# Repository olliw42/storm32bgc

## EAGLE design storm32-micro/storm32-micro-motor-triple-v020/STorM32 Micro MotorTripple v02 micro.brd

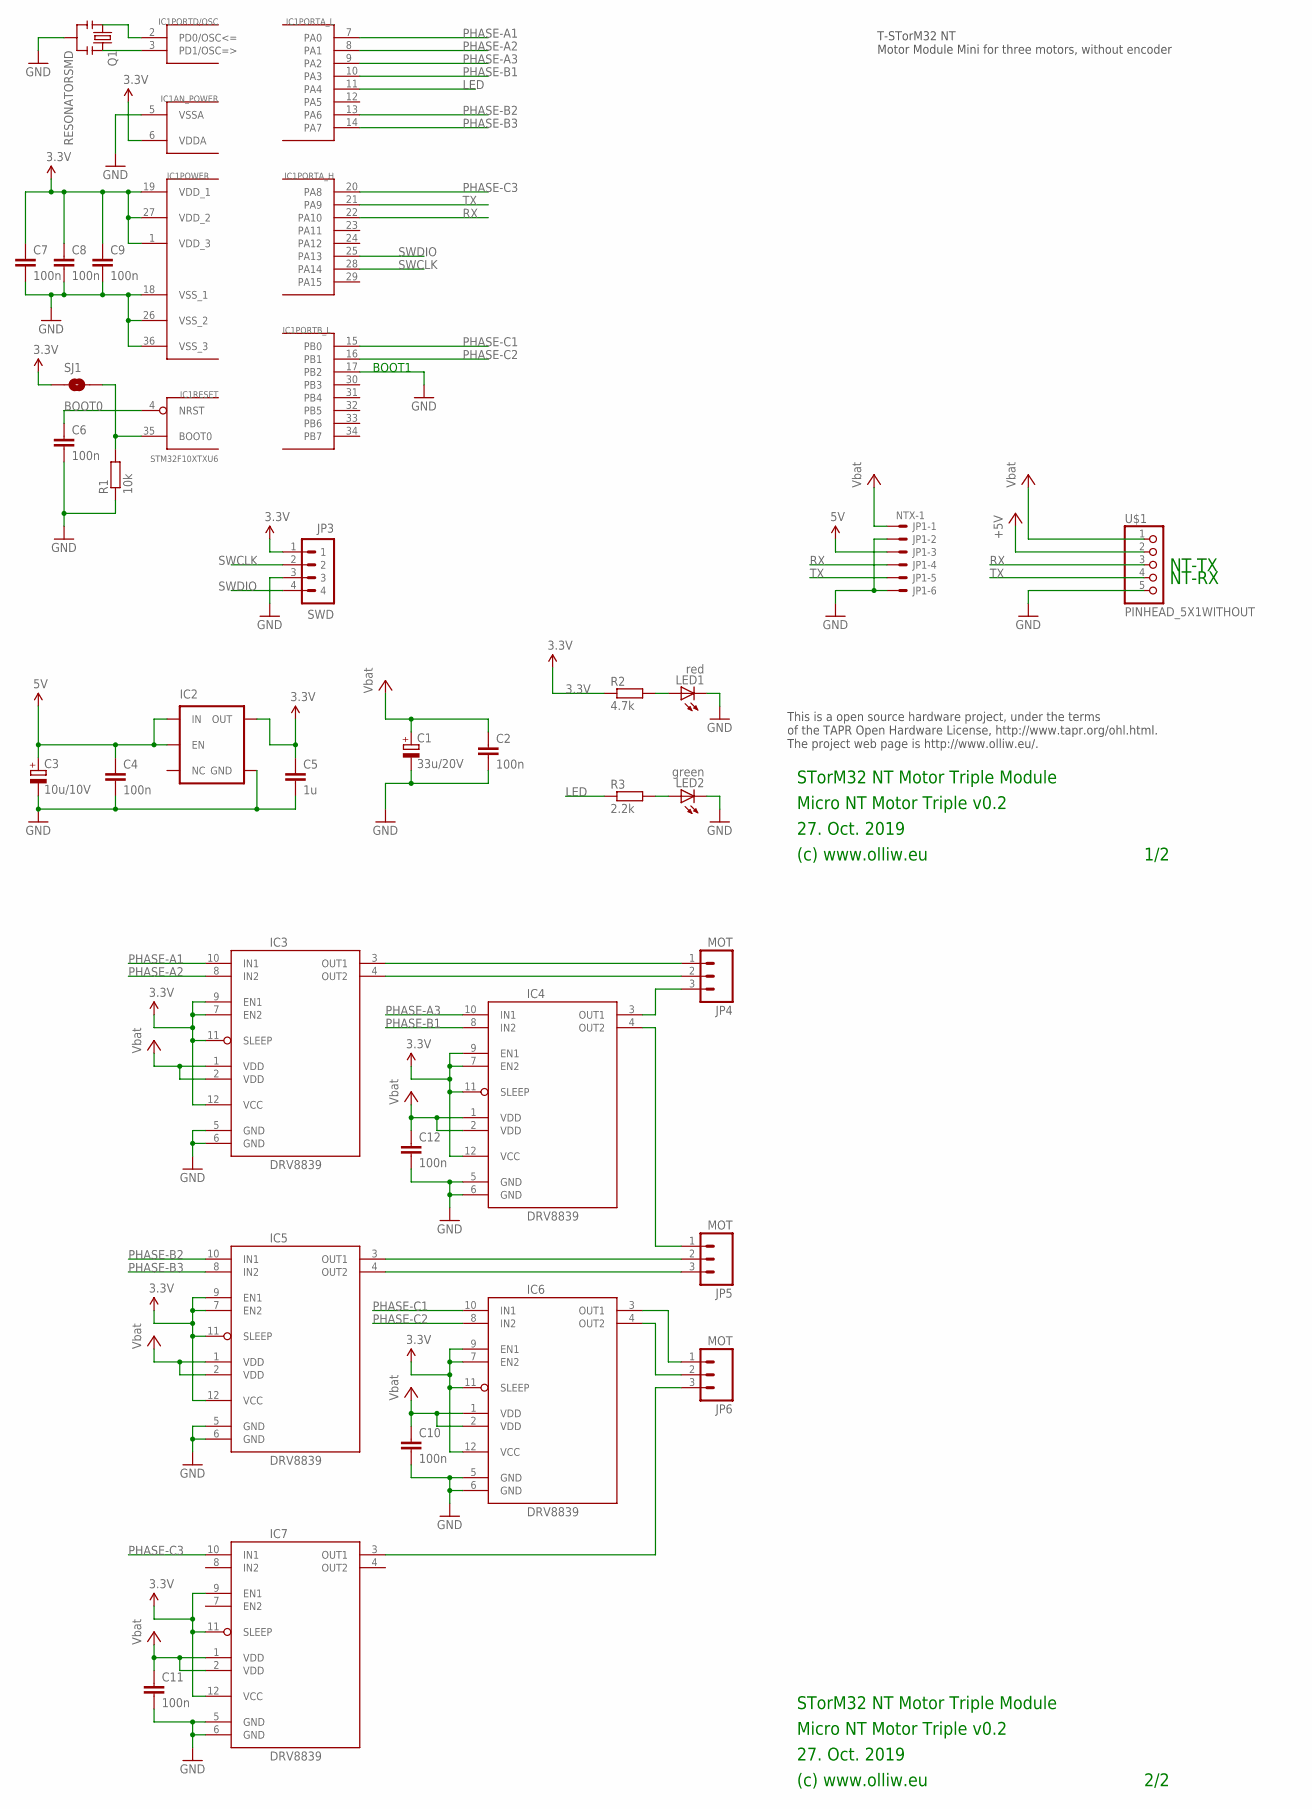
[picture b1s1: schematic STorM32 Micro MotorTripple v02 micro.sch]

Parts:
C1: 33u/20V; SMC_B
C2, C10, C11, C12: 100n; C0603
C3: 10u/10V; SMC_A
C4, C6, C7, C8, C9: 100n; C0402
C5: 1u; C0603
IC1: STM32F10XTXU6; VFQFPN36
IC2: V_REG_TPS76433SOT23-5; SOT23-5
IC3, IC4, IC5, IC6, IC7: DRV8839; WSON-12-2X3MM
JP1: NTX-1; SM06B-SRSS-TB
JP3: SWD; 4X1_1P27_OCT_BILEX
JP4, JP5, JP6: MOT; 1X03
LED1: red; CHIPLED_0603
LED2: green; CHIPLED_0603
Q1: RESONATORSMD; RESONATOR-SMD
R1: 10k; R0402
R2: 4.7k; R0402
R3: 2.2k; R0402
SJ1: BOOT0; SJ_2S-NO
U$1: PINHEAD_5X1WITHOUT; PINHEAD_5X1_WO

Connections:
3.3V: C5.1, C7.1, C8.1, C9.1, IC1.1 (VDD_3), IC1.6 (VDDA), IC1.19 (VDD_1), IC1.27 (VDD_2), IC2.5 (OUT), IC3.7 (EN2), IC3.9 (EN1), IC3.11 (SLEEP), IC3.12 (VCC), IC4.7 (EN2), IC4.9 (EN1), IC4.11 (SLEEP), IC4.12 (VCC), IC5.7 (EN2), IC5.9 (EN1), IC5.11 (SLEEP), IC5.12 (VCC), IC6.7 (EN2), IC6.9 (EN1), IC6.11 (SLEEP), IC6.12 (VCC), IC7.9 (EN1), IC7.11 (SLEEP), IC7.12 (VCC), JP3.1, R2.1, SJ1.1
5V: C3.+, C4.1, IC2.1 (IN), IC2.3 (EN), JP1.3, U$1.2
GND: C1.-, C2.2, C3.-, C4.2, C5.2, C6.2, C7.2, C8.2, C9.2, C10.2, C11.2, C12.2, IC1.5 (VSSA), IC1.17 (PB2), IC1.18 (VSS_1), IC1.26 (VSS_2), IC1.36 (VSS_3), IC2.2 (GND), IC3.5 (GND), IC3.6 (GND), IC4.5 (GND), IC4.6 (GND), IC5.5 (GND), IC5.6 (GND), IC6.5 (GND), IC6.6 (GND), IC7.5 (GND), IC7.6 (GND), JP1.2, JP1.6, JP3.3, LED1.C, LED2.C, Q1.2, R1.1, U$1.5
LED: IC1.11 (PA4), R3.1
unnamed: IC4.3 (OUT1), JP4.3
unnamed: C6.1, IC1.4 (NRST)
unnamed: IC1.35 (BOOT0), R1.2, SJ1.2
unnamed: IC1.2 (PD0/OSC<=), Q1.1
unnamed: IC1.3 (PD1/OSC=>), Q1.3
unnamed: LED1.A, R2.2
unnamed: LED2.A, R3.2
unnamed: IC6.3 (OUT1), JP6.1
unnamed: IC3.4 (OUT2), JP4.2
unnamed: IC3.3 (OUT1), JP4.1
unnamed: IC5.3 (OUT1), JP5.2
unnamed: IC4.4 (OUT2), JP5.1
unnamed: IC5.4 (OUT2), JP5.3
unnamed: IC6.4 (OUT2), JP6.2
unnamed: IC7.3 (OUT1), JP6.3
PHASE-A1: IC1.7 (PA0), IC3.10 (IN1)
PHASE-A2: IC1.8 (PA1), IC3.8 (IN2)
PHASE-A3: IC1.9 (PA2), IC4.10 (IN1)
PHASE-B1: IC1.10 (PA3), IC4.8 (IN2)
PHASE-B2: IC1.13 (PA6), IC5.10 (IN1)
PHASE-B3: IC1.14 (PA7), IC5.8 (IN2)
PHASE-C1: IC1.15 (PB0), IC6.10 (IN1)
PHASE-C2: IC1.16 (PB1), IC6.8 (IN2)
PHASE-C3: IC1.20 (PA8), IC7.10 (IN1)
RX: IC1.22 (PA10), JP1.4, U$1.3
SWCLK: IC1.28 (PA14), JP3.2
SWDIO: IC1.25 (PA13), JP3.4
TX: IC1.21 (PA9), JP1.5, U$1.4
VCCG: C1.+, C2.1, C10.1, C11.1, C12.1, IC3.1 (VDD), IC3.2 (VDD), IC4.1 (VDD), IC4.2 (VDD), IC5.1 (VDD), IC5.2 (VDD), IC6.1 (VDD), IC6.2 (VDD), IC7.1 (VDD), IC7.2 (VDD), JP1.1, U$1.1

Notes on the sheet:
27. Oct. 2019
(c) www.olliw.eu
STorM32 NT Motor Triple Module
Micro NT Motor Triple v0.2
T-STorM32 NT Motor Module Mini for three motors, without encoder
BOOT1
NT-TX
NT-RX
This is a open source hardware project, under the terms of the TAPR Open Hardware License, http://www.tapr.org/ohl.html. The project web page is http://www.olliw.eu/.
1/2
2/2

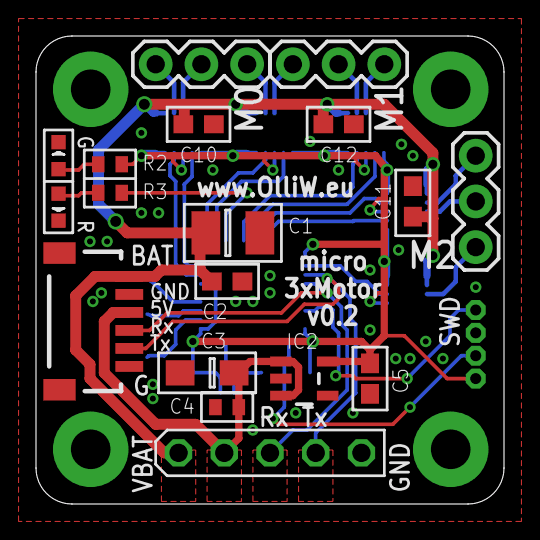
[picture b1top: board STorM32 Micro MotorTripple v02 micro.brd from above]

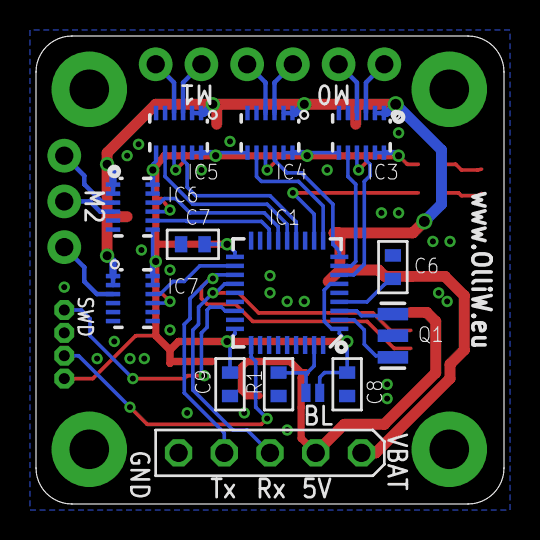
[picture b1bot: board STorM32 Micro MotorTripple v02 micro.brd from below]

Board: 2 copper layers, 26.0 x 26.0 mm, 32 parts (14 on the bottom side), 33 nets.

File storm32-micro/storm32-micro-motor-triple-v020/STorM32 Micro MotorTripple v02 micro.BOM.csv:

"Part";"Value";"Device";"Package";"Description";"";
"C1";"33u/20V";"CPOL-EUSMCB";"SMC_B";"POLARIZED CAPACITOR, European symbol";"";
"C2";"100n";"C-EUC0603";"C0603";"CAPACITOR, European symbol";"";
"C3";"10u/10V";"CPOL-EUSMCA";"SMC_A";"POLARIZED CAPACITOR, European symbol";"";
"C4";"100n";"C-EUC0402";"C0402";"CAPACITOR, European symbol";"";
"C5";"1u";"C-EUC0603";"C0603";"CAPACITOR, European symbol";"";
"C6";"100n";"C-EUC0402";"C0402";"CAPACITOR, European symbol";"";
"C7";"100n";"C-EUC0402";"C0402";"CAPACITOR, European symbol";"";
"C8";"100n";"C-EUC0402";"C0402";"CAPACITOR, European symbol";"";
"C9";"100n";"C-EUC0402";"C0402";"CAPACITOR, European symbol";"";
"C10";"100n";"C-EUC0603";"C0603";"CAPACITOR, European symbol";"";
"C11";"100n";"C-EUC0603";"C0603";"CAPACITOR, European symbol";"";
"C12";"100n";"C-EUC0603";"C0603";"CAPACITOR, European symbol";"";
"IC1";"STM32F10XTXU6";"STM32F10XTXU6";"VFQFPN36";"STM32F101/103 36pad VFQPFN36";"";
"IC2";"";"V_REG_TPS76433SOT23-5";"SOT23-5";"Voltage Regulator";"";
"IC3";"DRV8839";"DRV8839";"WSON-12-2X3MM";"";"";
"IC4";"DRV8839";"DRV8839";"WSON-12-2X3MM";"";"";
"IC5";"DRV8839";"DRV8839";"WSON-12-2X3MM";"";"";
"IC6";"DRV8839";"DRV8839";"WSON-12-2X3MM";"";"";
"IC7";"DRV8839";"DRV8839";"WSON-12-2X3MM";"";"";
"JP1";"NTX-1";"SM06B-SRSS-TB";"SM06B-SRSS-TB";"Disconnectable Crimp style connector, 1.0mm pitch6 contacts";"";
"JP3";"SWD";"P4X1_1P27-OCT_BILEX";"4X1_1P27_OCT_BILEX";"";"";
"JP4";"MOT";"M03PTH";"1X03";"Header 3";"";
"JP5";"MOT";"M03PTH";"1X03";"Header 3";"";
"JP6";"MOT";"M03PTH";"1X03";"Header 3";"";
"LED1";"red";"LEDCHIPLED_0603";"CHIPLED_0603";"LED";"";
"LED2";"green";"LEDCHIPLED_0603";"CHIPLED_0603";"LED";"";
"Q1";"RESONATORSMD";"RESONATORSMD";"RESONATOR-SMD";"Resonator";"";
"R1";"10k";"R-EU_R0402";"R0402";"RESISTOR, European symbol";"";
"R2";"4.7k";"R-EU_R0402";"R0402";"RESISTOR, European symbol";"";
"R3";"2.2k";"R-EU_R0402";"R0402";"RESISTOR, European symbol";"";
"SJ1";"BOOT0";"SOLDERJUMPERNO";"SJ_2S-NO";"Solder Jumper";"";
"U$1";"PINHEAD_5X1WITHOUT";"PINHEAD_5X1WITHOUT";"PINHEAD_5X1_WO";"";"";

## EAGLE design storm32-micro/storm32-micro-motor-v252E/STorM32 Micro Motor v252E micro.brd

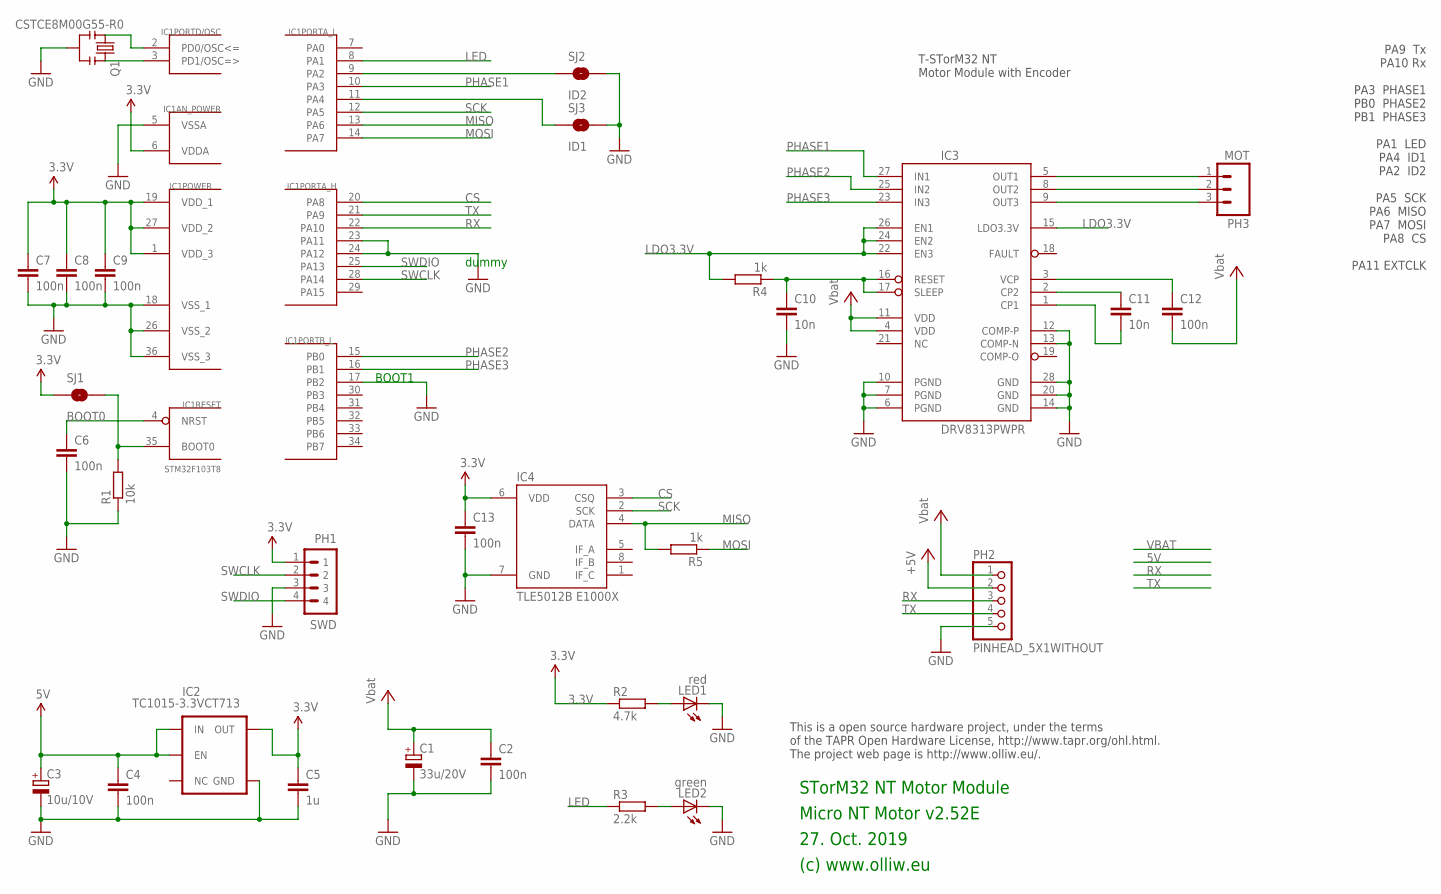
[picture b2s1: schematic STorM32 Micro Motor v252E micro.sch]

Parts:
C1: 33u/20V; SMC_C
C2, C4, C12: 100n; C0603
C3: 10u/10V; SMC_B
C5: 1u; C0603
C6, C7, C8, C9, C13: 100n; C0402
C10: 10n; C0402
C11: 10n; C0603
IC1: STM32F103T8; VFQFPN36
IC2: TC1015-3.3VCT713; SOT23-5
IC3: DRV8313PWPR; HTSSOP28
IC4: TLE5012B E1000X; SO08
LED1: red; CHIPLED_0603
LED2: green; CHIPLED_0603
PH1: SWD; 4X1_1P27_OCT_BILEX
PH2: PINHEAD_5X1WITHOUT; PINHEAD_5X1_WO
PH3: MOT; 1X03_NO_SILK
Q1: CSTCE8M00G55-R0; RESONATOR-SMD
R1: 10k; R0402
R2: 4.7k; R0402
R3: 2.2k; R0402
R4, R5: 1k; R0402
SJ1: BOOT0; SJ_2S-NO
SJ2: ID2; SJ_2S-NO
SJ3: ID1; SJ_2S-NO

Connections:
3.3V: C5.1, C7.1, C8.1, C9.1, C13.1, IC1.1 (VDD_3), IC1.6 (VDDA), IC1.19 (VDD_1), IC1.27 (VDD_2), IC2.5 (OUT), IC4.6 (VDD), PH1.1, R2.1, SJ1.1
5V: C3.+, C4.1, IC2.1 (IN), IC2.3 (EN), PH2.2
CS: IC1.20 (PA8), IC4.3 (CSQ)
GND: C1.-, C2.2, C3.-, C4.2, C5.2, C6.2, C7.2, C8.2, C9.2, C10.2, C13.2, IC1.5 (VSSA), IC1.17 (PB2), IC1.18 (VSS_1), IC1.23 (PA11), IC1.24 (PA12), IC1.26 (VSS_2), IC1.36 (VSS_3), IC2.2 (GND), IC3.6 (PGND), IC3.7 (PGND), IC3.10 (PGND), IC3.12 (COMP-P), IC3.13 (COMP-N), IC3.14 (GND), IC3.20 (GND), IC3.28 (GND), IC4.7 (GND), LED1.C, LED2.C, PH1.3, PH2.5, Q1.2, R1.1, SJ2.2, SJ3.2
LDO3.3V: IC3.15 (LDO3.3V), IC3.22 (EN3), IC3.24 (EN2), IC3.26 (EN1), R4.2
LED: IC1.8 (PA1), R3.1
M1: IC3.5 (OUT1), PH3.1
M2: IC3.8 (OUT2), PH3.2
M3: IC3.9 (OUT3), PH3.3
MISO: IC1.13 (PA6), IC4.4 (DATA), R5.2
MOSI: IC1.14 (PA7), R5.1
unnamed: IC1.9 (PA2), SJ2.1
unnamed: IC1.11 (PA4), SJ3.1
unnamed: C6.1, IC1.4 (NRST)
unnamed: IC1.35 (BOOT0), R1.2, SJ1.2
unnamed: IC1.2 (PD0/OSC<=), Q1.1
unnamed: IC1.3 (PD1/OSC=>), Q1.3
unnamed: LED1.A, R2.2
unnamed: LED2.A, R3.2
unnamed: C11.1, IC3.2 (CP2)
unnamed: C11.2, IC3.1 (CP1)
unnamed: C10.1, IC3.16 (RESET), IC3.17 (SLEEP), R4.1
unnamed: C12.1, IC3.3 (VCP)
PHASE1: IC1.10 (PA3), IC3.27 (IN1)
PHASE2: IC1.15 (PB0), IC3.25 (IN2)
PHASE3: IC1.16 (PB1), IC3.23 (IN3)
RX: IC1.22 (PA10), PH2.3
SCK: IC1.12 (PA5), IC4.2 (SCK)
SWCLK: IC1.28 (PA14), PH1.2
SWDIO: IC1.25 (PA13), PH1.4
TX: IC1.21 (PA9), PH2.4
VBAT: C1.+, C2.1, C12.2, IC3.4 (VDD), IC3.11 (VDD), PH2.1

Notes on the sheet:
27. Oct. 2019
(c) www.olliw.eu
STorM32 NT Motor Module
Micro NT Motor v2.52E
This is a open source hardware project, under the terms of the TAPR Open Hardware License, http://www.tapr.org/ohl.html. The project web page is http://www.olliw.eu/.
T-STorM32 NT Motor Module with Encoder
BOOT1
PA9 Tx PA10 Rx PA3 PHASE1 PB0 PHASE2 PB1 PHASE3 PA1 LED PA4 ID1 PA2 ID2 PA5 SCK PA6 MISO PA7 MOSI PA8 CS PA11 EXTCLK
dummy

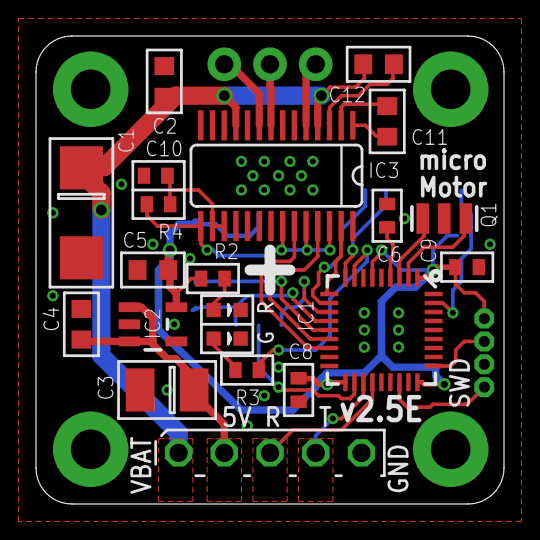
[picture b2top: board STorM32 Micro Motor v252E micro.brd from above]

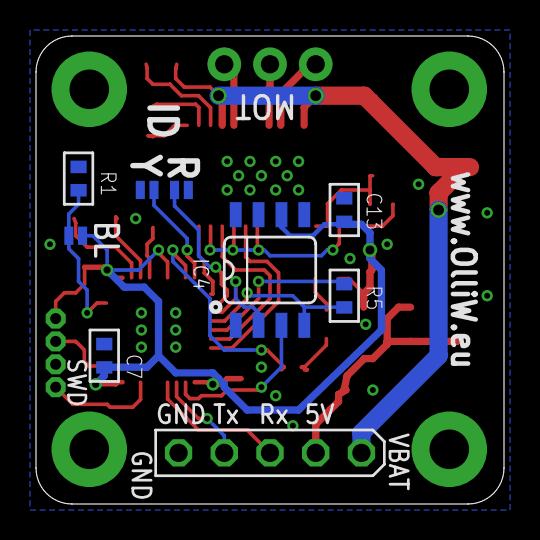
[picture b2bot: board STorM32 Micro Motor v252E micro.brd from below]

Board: 2 copper layers, 26.0 x 26.0 mm, 31 parts (9 on the bottom side), 32 nets.

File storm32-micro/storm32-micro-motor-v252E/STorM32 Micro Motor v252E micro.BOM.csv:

"Part";"Value";"Device";"Package";"Description";"";
"C1";"33u/20V";"CPOL-EUSMCC";"SMC_C";"POLARIZED CAPACITOR, European symbol";"";
"C2";"100n";"C-EUC0603";"C0603";"CAPACITOR, European symbol";"";
"C3";"10u/10V";"CPOL-EUSMCB";"SMC_B";"POLARIZED CAPACITOR, European symbol";"";
"C4";"100n";"C-EUC0603";"C0603";"CAPACITOR, European symbol";"";
"C5";"1u";"C-EUC0603";"C0603";"CAPACITOR, European symbol";"";
"C6";"100n";"C-EUC0402";"C0402";"CAPACITOR, European symbol";"";
"C7";"100n";"C-EUC0402";"C0402";"CAPACITOR, European symbol";"";
"C8";"100n";"C-EUC0402";"C0402";"CAPACITOR, European symbol";"";
"C9";"100n";"C-EUC0402";"C0402";"CAPACITOR, European symbol";"";
"C10";"10n";"C-EUC0402";"C0402";"CAPACITOR, European symbol";"";
"C11";"10n";"C-EUC0603";"C0603";"CAPACITOR, European symbol";"";
"C12";"100n";"C-EUC0603";"C0603";"CAPACITOR, European symbol";"";
"C13";"100n";"C-EUC0402";"C0402";"CAPACITOR, European symbol";"";
"IC1";"STM32F103T8";"STM32F10XTXU6";"VFQFPN36";"STM32F101/103 36pad VFQPFN36";"";
"IC2";"TC1015-3.3VCT713";"V_REG_TPS76433SOT23-5";"SOT23-5";"Voltage Regulator";"";
"IC3";"DRV8313PWPR";"DRV8313";"HTSSOP28";"";"";
"IC4";"TLE5012B E1000X";"TLE5012B";"SO08";"";"";
"LED1";"red";"LEDCHIPLED_0603";"CHIPLED_0603";"LED";"";
"LED2";"green";"LEDCHIPLED_0603";"CHIPLED_0603";"LED";"";
"PH1";"SWD";"P4X1_1P27-OCT_BILEX";"4X1_1P27_OCT_BILEX";"";"";
"PH2";"PINHEAD_5X1WITHOUT";"PINHEAD_5X1WITHOUT";"PINHEAD_5X1_WO";"";"";
"PH3";"MOT";"M031X03_NO_SILK";"1X03_NO_SILK";"Header 3";"";
"Q1";"CSTCE8M00G55-R0";"RESONATORSMD";"RESONATOR-SMD";"Resonator";"";
"R1";"10k";"R-EU_R0402";"R0402";"RESISTOR, European symbol";"";
"R2";"4.7k";"R-EU_R0402";"R0402";"RESISTOR, European symbol";"";
"R3";"2.2k";"R-EU_R0402";"R0402";"RESISTOR, European symbol";"";
"R4";"1k";"R-EU_R0402";"R0402";"RESISTOR, European symbol";"";
"R5";"1k";"R-EU_R0402";"R0402";"RESISTOR, European symbol";"";
"SJ1";"BOOT0";"SOLDERJUMPERNO";"SJ_2S-NO";"Solder Jumper";"";
"SJ2";"ID2";"SOLDERJUMPERNO";"SJ_2S-NO";"Solder Jumper";"";
"SJ3";"ID1";"SOLDERJUMPERNO";"SJ_2S-NO";"Solder Jumper";"";

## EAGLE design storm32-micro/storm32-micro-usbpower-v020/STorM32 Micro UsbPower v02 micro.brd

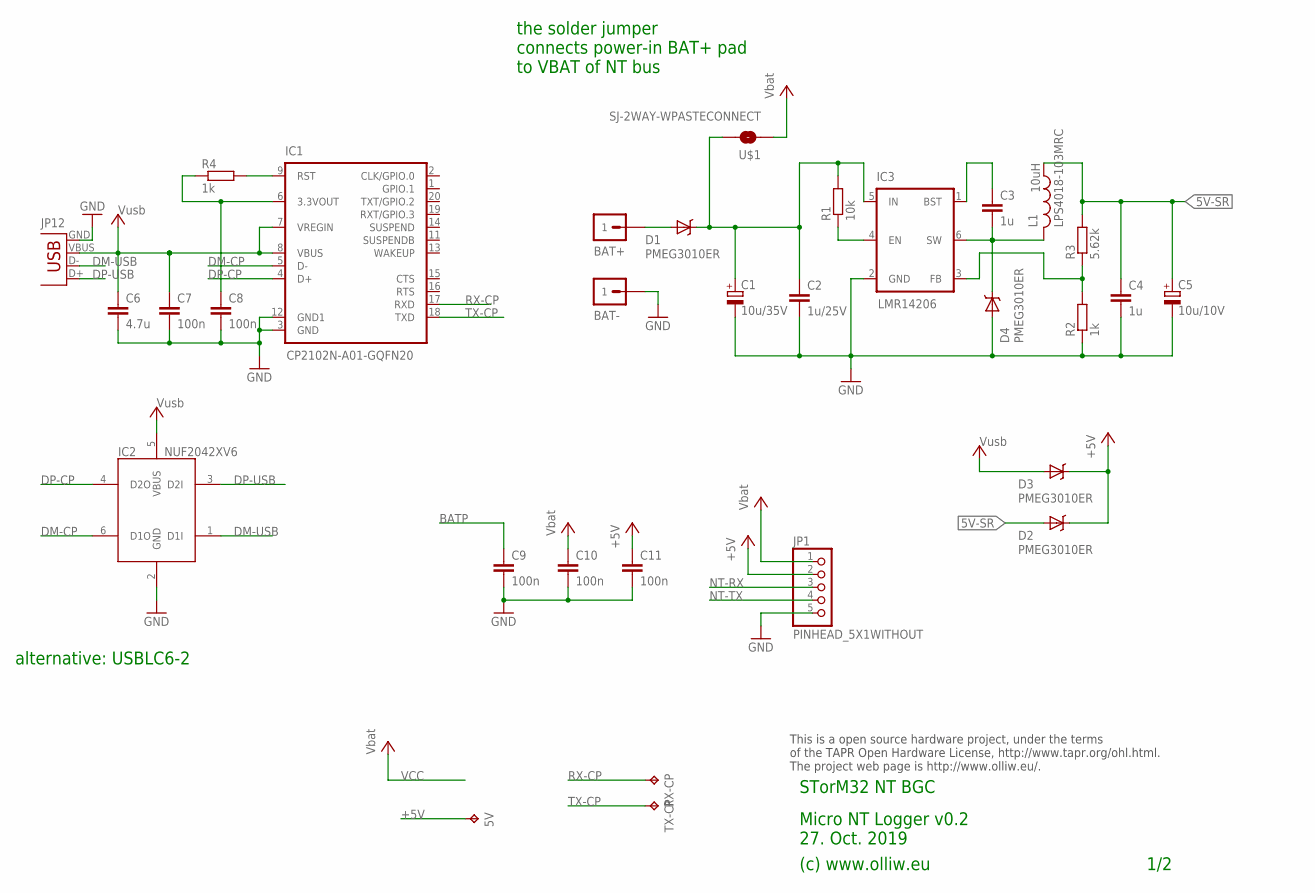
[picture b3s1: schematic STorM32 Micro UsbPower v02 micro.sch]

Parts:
5V: TPB1,27; B1,27
BAT+: M1X1; 1X1_WITHOUT
BAT-: M1X1; 1X1_WITHOUT
C1: 10u/35V; SMC_B
C2: 1u/25V; C0603
C3, C4: 1u; C0603
C5: 10u/10V; SMC_A
C6: 4.7u; C0603
C7, C8, C11: 100n; C0402
C9, C10: 100n; C0603
D1, D2, D3, D4: PMEG3010ER; SOD123W-DIODE
IC1: CP2102N-A01-GQFN20; QFN20-CP2102N
IC2: NUF2042XV6; SOT563-6
IC3: LMR14206; SOT23-6
JP1: PINHEAD_5X1WITHOUT; PINHEAD_5X1_WO
L1: LPS4018-103MRC; L4X4
R1: 10k; R0402
R2, R4: 1k; R0402
R3: 5.62k; R0402
RX-CP: TPB1,27; B1,27
TX-CP: TPB1,27; B1,27
U$1: SJ-2WAY-WPASTECONNECT; SJ-2WAY-BIG-WPASTEC
USB: Amphenol 10118192-0001LF; USB-MICROB

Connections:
3.3V-CP2102: C8.1, IC1.6 (3.3VOUT), R4.1
5V-SR: C4.1, C5.+, D2.A, L1.1, R3.2
+5V: 5V.TP, C11.1, D2.C, D3.C, JP1.2
BATP: BAT+.1, C9.1, D1.A
DM-CP: IC1.5 (D-), IC2.6 (D1O)
DM-USB: IC2.1 (D1I), USB.D-
DP-CP: IC1.4 (D+), IC2.4 (D2O)
DP-USB: IC2.3 (D2I), USB.D+
GND: BAT-.1, C1.-, C2.2, C4.2, C5.-, C6.2, C7.2, C8.2, C9.2, C10.2, C11.2, D4.A, IC1.3 (GND), IC1.12 (GND1), IC2.2 (GND), IC3.2 (GND), JP1.5, R2.1, USB.GND
unnamed: C1.+, C2.1, D1.C, IC3.5 (IN), R1.2, U$1.2
unnamed: IC3.4 (EN), R1.1
unnamed: C3.1, IC3.1 (BST)
unnamed: IC3.3 (FB), R2.2, R3.1
unnamed: C3.2, D4.C, IC3.6 (SW), L1.2
unnamed: IC1.9 (RST), R4.2
NT-RX: JP1.3
NT-TX: JP1.4
RX-CP: IC1.17 (RXD), RX-CP.TP
TX-CP: IC1.18 (TXD), TX-CP.TP
VCC: C10.1, JP1.1, U$1.1
VUSB: C6.1, C7.1, D3.A, IC1.7 (VREGIN), IC1.8 (VBUS), IC2.5 (VBUS), USB.VBUS

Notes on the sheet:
JP12
10uH
(c) www.olliw.eu
STorM32 NT BGC
This is a open source hardware project, under the terms of the TAPR Open Hardware License, http://www.tapr.org/ohl.html. The project web page is http://www.olliw.eu/.
1/2
Micro NT Logger v0.2 27. Oct. 2019
alternative: USBLC6-2
the solder jumper connects power-in BAT+ pad to VBAT of NT bus

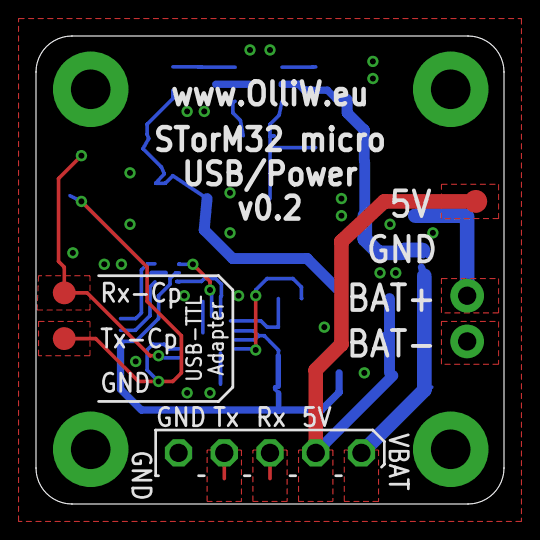
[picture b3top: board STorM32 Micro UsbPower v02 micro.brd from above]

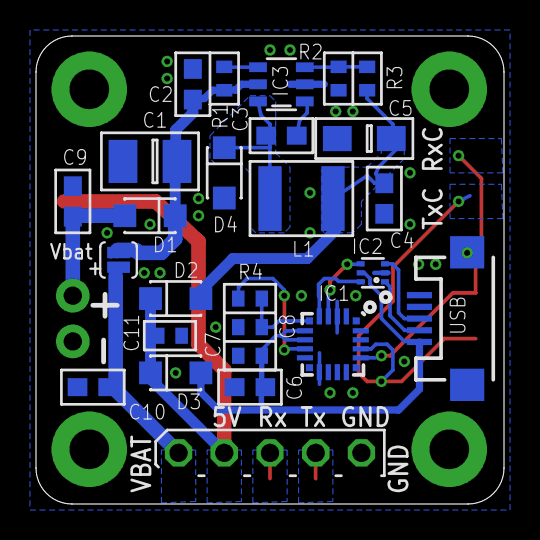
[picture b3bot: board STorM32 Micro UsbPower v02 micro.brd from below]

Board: 2 copper layers, 26.0 x 26.0 mm, 31 parts (25 on the bottom side), 19 nets.

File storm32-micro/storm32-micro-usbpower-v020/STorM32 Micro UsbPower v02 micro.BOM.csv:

"Part";"Value";"Device";"Package";"Description";"TP_SIGNAL_NAME";
"5V";"TPB1,27";"TPB1,27";"B1,27";"Test pad";"";
"BAT+";"";"M1X1";"1X1_WITHOUT";"";"";
"BAT-";"";"M1X1";"1X1_WITHOUT";"";"";
"C1";"10u/35V";"CPOL-EUSMCB";"SMC_B";"POLARIZED CAPACITOR, European symbol";"";
"C2";"1u/25V";"C-EUC0603";"C0603";"CAPACITOR, European symbol";"";
"C3";"1u";"C-EUC0603";"C0603";"CAPACITOR, European symbol";"";
"C4";"1u";"C-EUC0603";"C0603";"CAPACITOR, European symbol";"";
"C5";"10u/10V";"CPOL-EUSMCA";"SMC_A";"POLARIZED CAPACITOR, European symbol";"";
"C6";"4.7u";"C-EUC0603";"C0603";"CAPACITOR, European symbol";"";
"C7";"100n";"C-EUC0402";"C0402";"CAPACITOR, European symbol";"";
"C8";"100n";"C-EUC0402";"C0402";"CAPACITOR, European symbol";"";
"C9";"100n";"C-EUC0603";"C0603";"CAPACITOR, European symbol";"";
"C10";"100n";"C-EUC0603";"C0603";"CAPACITOR, European symbol";"";
"C11";"100n";"C-EUC0402";"C0402";"CAPACITOR, European symbol";"";
"D1";"PMEG3010ER";"DIODE-SCHOTTKYSOD123-W";"SOD123W-DIODE";"";"";
"D2";"PMEG3010ER";"DIODE-SCHOTTKYSOD123-W";"SOD123W-DIODE";"";"";
"D3";"PMEG3010ER";"DIODE-SCHOTTKYSOD123-W";"SOD123W-DIODE";"";"";
"D4";"PMEG3010ER";"DIODE-SCHOTTKYSOD123-W";"SOD123W-DIODE";"";"";
"IC1";"CP2102N-A01-GQFN20";"CP2102N-QFN20";"QFN20-CP2102N";"";"";
"IC2";"NUF2042XV6";"NUF2042XV6";"SOT563-6";"";"";
"IC3";"LMR14206";"MP2359";"SOT23-6";"";"";
"JP1";"PINHEAD_5X1WITHOUT";"PINHEAD_5X1WITHOUT";"PINHEAD_5X1_WO";"";"";
"L1";"LPS4018-103MRC";"L";"L4X4";"";"";
"R1";"10k";"R-EU_R0402";"R0402";"RESISTOR, European symbol";"";
"R2";"1k";"R-EU_R0402";"R0402";"RESISTOR, European symbol";"";
"R3";"5.62k";"R-EU_R0402";"R0402";"RESISTOR, European symbol";"";
"R4";"1k";"R-EU_R0402";"R0402";"RESISTOR, European symbol";"";
"RX-CP";"TPB1,27";"TPB1,27";"B1,27";"Test pad";"";
"TX-CP";"TPB1,27";"TPB1,27";"B1,27";"Test pad";"";
"U$1";"SJ-2WAY-WPASTECONNECT";"SJ-2WAY-WPASTECONNECT";"SJ-2WAY-BIG-WPASTEC";"";"";
"USB";"Amphenol 10118192-0001LF";"USB-MICROB";"USB-MICROB";"USB Connectors";"";

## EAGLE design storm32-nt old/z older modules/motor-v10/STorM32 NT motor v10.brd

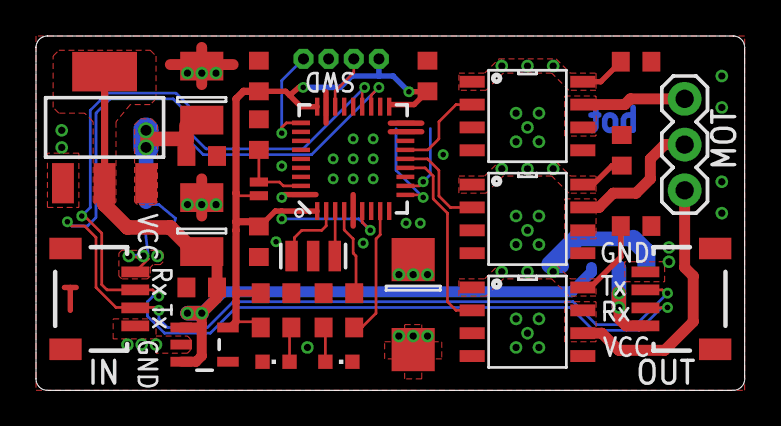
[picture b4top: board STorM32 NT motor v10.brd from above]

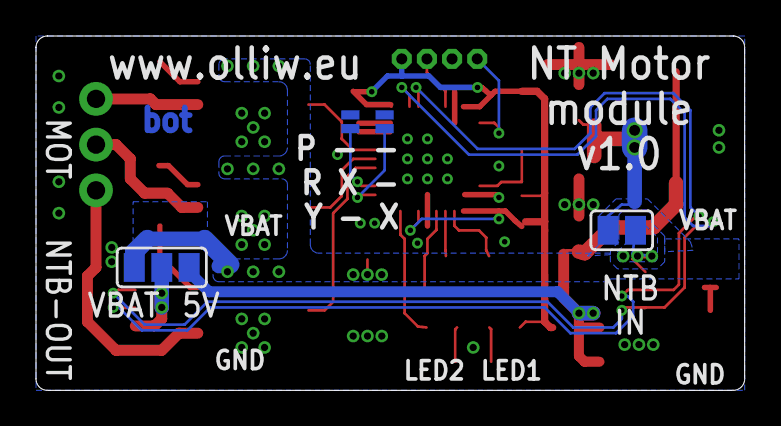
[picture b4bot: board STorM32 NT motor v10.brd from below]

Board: 2 copper layers, 39.4 x 19.7 mm, 34 parts (4 on the bottom side), 25 nets.

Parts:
C1: 33u/20V; SMC_C
C2, C3, C4, C6, C8, C9, C10, C11, C14: 100n; C0603
C5: 10u/6.3V; SMC_B
C7: 1u; C0603
C12: 10u/20V; SMC_B
IC1: NCP1117ST50T3G; SOT223
IC2: SOT23-5
JP2: SWD; 4X1_1P27_OCT_BILEX
LED1: red; CHIPLED_0603
LED2: green; CHIPLED_0603
MOT: 1X03
NTB-IN: NTB1; SM04B-SRSS-TB
NTB-OUT: NTB2; SM04B-SRSS-TB
R1: 4.7k; R0603
R6: 2.2k; R0603
R7: 10k; R0603
SJ1: SJ_2
SJ2: BOOT0; SJ_2S-NO
SJ3: ID2; SJ_2S-NO
SJ4: ID1; SJ_2S-NO
SJ5: SJ_1T
U1: STM32F10XTXU6; VFQFPN36
U$1, U$2, U$4: TC4452DFN08; DFN8
Y1: RESONATORSMD; RESONATOR-SMD

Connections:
3.3V: C7.1, C9.1, C10.1, C11.1, IC2.5, JP2.1, R1.1, SJ2.1, U1.1, U1.6, U1.19, U1.27
5V: C5.+, C6.1, IC1.2, IC1.4, IC2.1, IC2.3, SJ1.1
GND: C1.-, C2.2, C3.2, C4.2, C5.-, C6.2, C7.2, C8.2, C9.2, C10.2, C11.2, C12.-, C14.2, IC1.1, IC2.2, JP2.3, LED1.C, LED2.C, NTB-IN.4, NTB-OUT.4, R7.1, SJ3.2, SJ4.2, U1.5, U1.17, U1.18, U1.26, U1.36, U$1.3, U$1.4, U$1.5, U$2.3, U$2.4, U$2.5, U$4.3, U$4.4, U$4.5, Y1.2
LED: R6.1, U1.8
unnamed: MOT.2, U$2.6, U$2.7
unnamed: NTB-OUT.1, SJ1.2
unnamed: SJ3.1, U1.10
unnamed: SJ4.1, U1.11
unnamed: MOT.1, U$1.6, U$1.7
unnamed: MOT.3, U$4.6, U$4.7
unnamed: C8.1, U1.4
unnamed: R7.2, SJ2.2, U1.35
unnamed: U1.2, Y1.1
unnamed: U1.3, Y1.3
unnamed: LED1.A, R1.2
unnamed: LED2.A, R6.2
unnamed: NTB-IN.1, SJ5.3
PHASE1: U1.13, U$1.2
PHASE2: U1.14, U$2.2
PHASE3: U1.15, U$4.2
RX: NTB-IN.2, NTB-OUT.2, U1.22
SWCLK: JP2.4, U1.28
SWDIO: JP2.2, U1.25
TX: NTB-IN.3, NTB-OUT.3, U1.21
VBAT: C1.+, C2.1, C3.1, C4.1, C12.+, C14.1, IC1.3, SJ1.3, SJ5.1, U$1.1, U$1.8, U$2.1, U$2.8, U$4.1, U$4.8

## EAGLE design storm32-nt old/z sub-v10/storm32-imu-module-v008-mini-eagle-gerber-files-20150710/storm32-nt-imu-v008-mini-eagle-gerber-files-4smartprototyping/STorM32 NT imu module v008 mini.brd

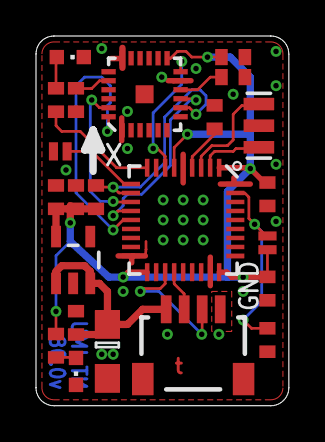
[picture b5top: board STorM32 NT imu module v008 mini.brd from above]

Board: 2 copper layers, 14.0 x 20.5 mm, 23 parts (0 on the bottom side), 20 nets.

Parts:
C1: 10u/6.3V; SMC_A
C2, C3, C6, C8, C9, C10, C11: 100n; C0402
C5: 2.2n; C0402
C7: 1u; C0402
IC1: MPU6000; QFN-24
IC2: SOT23-5
LED1: red; CHIPLED_0603
LED2: green; CHIPLED_0603
NTX: NTX; SM04B-SRSS-TB
R1: 4.7k; R0402
R5, R7: 10k; R0402
R6: 2.2k; R0402
SJ2: BOOT0; SJ_2S-NO
SJ3: IMU-ID; SJ_2S-NO
U1: STM32F10XTXU6; VFQFPN36
Y1: RESONATORSMD; RESONATOR-SMD

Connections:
3.3V: C3.1, C7.1, C9.1, C10.1, C11.1, IC1.13, IC2.5, R1.1, R5.2, SJ2.1, U1.1, U1.6, U1.19, U1.27
5V: C1.+, C2.1, IC2.1, IC2.3, NTX.1
CS: IC1.8, R5.1, U1.11
GND: C1.-, C2.2, C3.2, C5.2, C6.2, C7.2, C8.2, C9.2, C10.2, C11.2, IC1.1, IC1.11, IC1.18, IC2.2, LED1.C, LED2.C, NTX.4, R7.1, SJ3.1, U1.5, U1.17, U1.18, U1.26, U1.36, Y1.2
INT: IC1.12, U1.7
LED: R6.1, U1.9
unnamed: C8.1, U1.4
unnamed: LED2.A, R6.2
unnamed: R7.2, SJ2.2, U1.35
unnamed: U1.2, Y1.1
unnamed: U1.3, Y1.3
unnamed: LED1.A, R1.2
unnamed: C6.1, IC1.10
unnamed: C5.1, IC1.20
RX: NTX.2, U1.22
RX2: SJ3.2, U1.10
SCL: IC1.23, U1.12
SDA: IC1.24, U1.14
SDO: IC1.9, U1.13
TX: NTX.3, U1.21

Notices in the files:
parts and their libraries:
Licensing: CC v3.0 Share-Alike You are welcome to use this library for commercial purposes.
